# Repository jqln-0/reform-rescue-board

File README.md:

This is a breakout board for an MNT Reform's SOM! It's designed to make it
easier to rescue a bad bootloader flash, or work on the initial bring-up of new
SOMs.

Most of what it breaks out is already available on the Reform motherboard,
however USB1 is exposed as a micro usb port so that it's easy to use
manufacturer tools like `uuu` that rely on USB OTG functionality.

Here is what the PCB looks like in KiCad:

Here is what the PCB looks like in real life:

Here is what an assembled board that's in-use looks like:

(please excuse my bodges; I initially used one wrong part number + one wrong
footprint.)

Note the last picture includes the little STL in `enclosure/`. It's not very
good, but whatever. It'll do.

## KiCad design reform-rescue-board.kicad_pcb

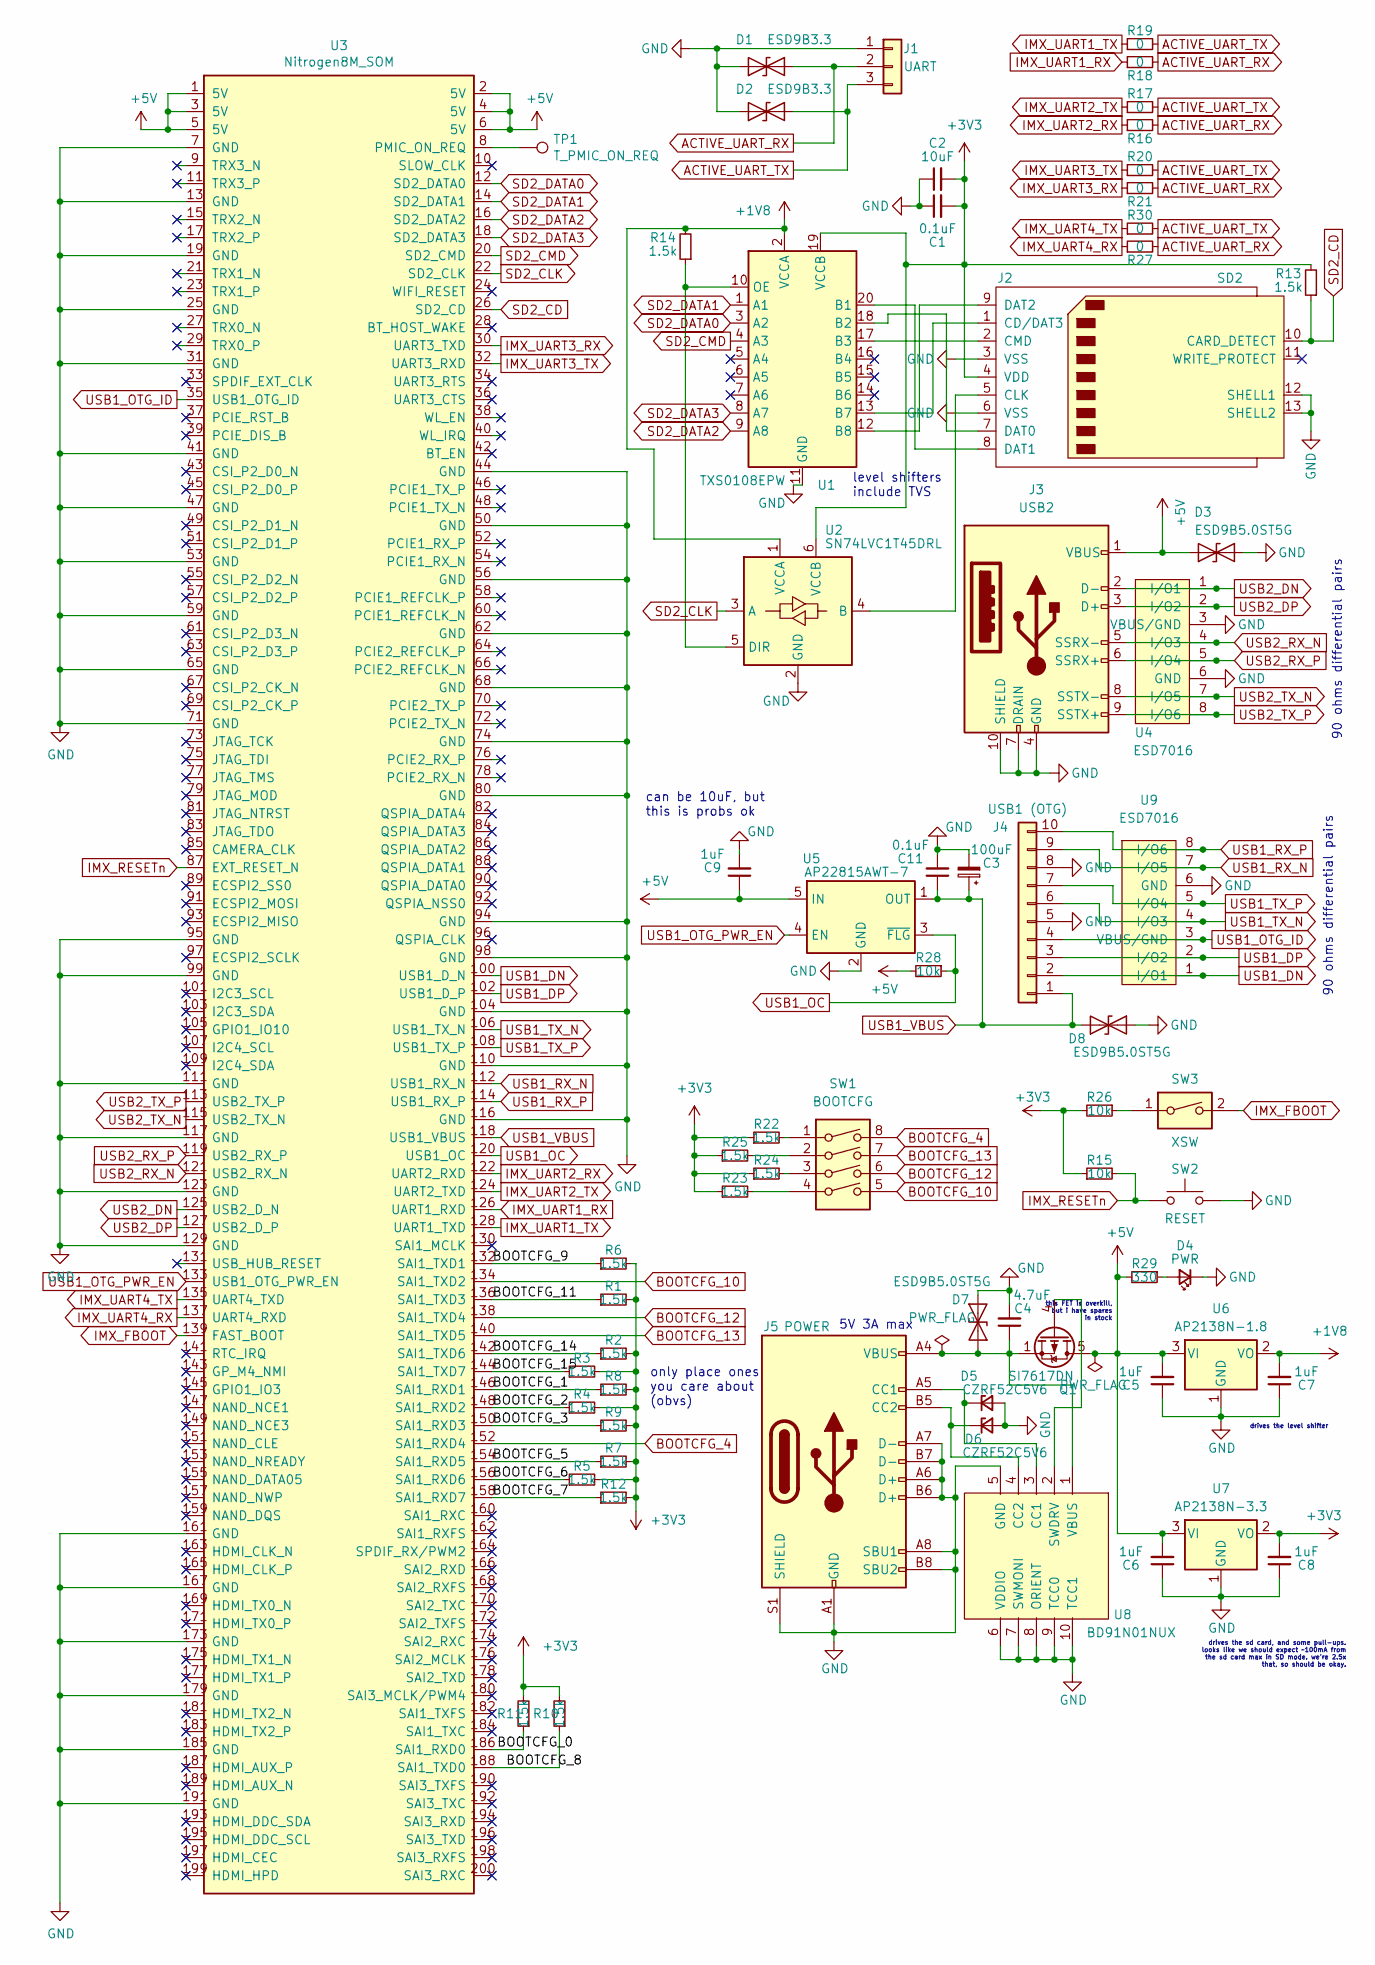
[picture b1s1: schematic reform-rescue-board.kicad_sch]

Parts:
C1, C11: 0.1uF; C_0603_1608Metric_Pad1.08x0.95mm_HandSolder
C2: 10uF; C_0603_1608Metric_Pad1.08x0.95mm_HandSolder
C3: 100uF; CP_Elec_6.3x5.8
C4: 4.7uF; C_0603_1608Metric_Pad1.08x0.95mm_HandSolder
C5, C6, C7, C8, C9: 1uF; C_0603_1608Metric_Pad1.08x0.95mm_HandSolder
D1, D2: ESD9B3.3; D_SOD-923
D3, D7, D8: ESD9B5.0ST5G; D_SOD-923
D4: PWR; D_0603_1608Metric
D5, D6: CZRF52C5V6; D_SOD-323_HandSoldering
J1: UART; PinHeader_1x03_P2.54mm_Vertical
J2: SD2; SD_Kyocera_145638109511859+
J3: USB2; USB3_A_Molex_48393-001
J4: USB1 (OTG); USB3_Micro-B_Connfly_DS1104-01
J5: POWER; USB_C_Receptacle_HRO_TYPE-C-31-M-12
Q1: SI7617DN; Vishay_PowerPAK_1212-8_Single
R1, R2, R3, R4, R5, R6, R7, R8, R9, R10, R11, R12, R13, R14, R22, R23, R24, R25: 1.5k; R_0603_1608Metric_Pad0.98x0.95mm_HandSolder
R15, R26, R28: 10k; R_0603_1608Metric_Pad0.98x0.95mm_HandSolder
R16, R17, R18, R19, R20, R21, R27, R30: 0; R_0603_1608Metric_Pad0.98x0.95mm_HandSolder
R29: 330; R_0603_1608Metric_Pad0.98x0.95mm_HandSolder
SW1: BOOTCFG; SW_DIP_SPSTx04_Slide_Omron_A6S-410x_W8.9mm_P2.54mm
SW2: RESET; SW_SPST_Omron_B3FS-100xP
SW3: XSW; SW_DIP_SPSTx01_Slide_Omron_A6S-110x_W8.9mm_P2.54mm
TP1: T_PMIC_ON_REQ; TestPoint_Pad_D1.0mm
U1: TXS0108EPW; TSSOP-20_4.4x6.5mm_P0.65mm
U2: SN74LVC1T45DRL; SOT-563
U3: Nitrogen8M_SOM; TE_2040910-1
U4, U9: ESD7016; TVS_ESD7016MUTAG
U5: AP22815AWT-7; SOT-23-5
U6: AP2138N-1.8; SOT-23
U7: AP2138N-3.3; SOT-23
U8: BD91N01NUX; VSON-10-1EP_3x3mm_P0.5mm_EP1.65x2.4mm

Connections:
+1V8: C7.2, R14.2, U1.2 (VCCA), U2.1 (VCCA), U6.2 (VO)
+3V3: C1.2, C2.2, C8.2, J2.4 (VDD), R1.2, R2.2, R3.2, R4.2, R5.2, R6.2, R7.2, R8.2, R9.2, R10.2, R11.2, R12.2, R13.2, R15.1, R22.1, R23.1, R24.1, R25.1, R26.2, U1.19 (VCCB), U2.6 (VCCB), U7.2 (VO)
+5V: C5.2, C6.2, C9.1, D3.1 (A1), J3.1 (VBUS), Q1.5 (D), R28.2, R29.2, U3.1 (5V), U3.2 (5V), U3.3 (5V), U3.4 (5V), U3.5 (5V), U3.6 (5V), U5.5 (IN), U6.3 (VI), U7.3 (VI)
/BOOTCFG_0: R11.1, U3.186 (SAI1_RXD0)
/BOOTCFG_1: R8.1, U3.146 (SAI1_RXD1)
/BOOTCFG_2: R4.1, U3.148 (SAI1_RXD2)
/BOOTCFG_3: R9.1, U3.150 (SAI1_RXD3)
/BOOTCFG_5: R7.1, U3.154 (SAI1_RXD5)
/BOOTCFG_6: R5.1, U3.156 (SAI1_RXD6)
/BOOTCFG_7: R12.1, U3.158 (SAI1_RXD7)
/BOOTCFG_8: R10.1, U3.188 (SAI1_TXD0)
/BOOTCFG_9: R6.1, U3.132 (SAI1_TXD1)
/BOOTCFG_11: R1.1, U3.136 (SAI1_TXD3)
/BOOTCFG_14: R2.1, U3.142 (SAI1_TXD6)
/BOOTCFG_15: R3.1, U3.144 (SAI1_TXD7)
ACTIVE_UART_RX: D1.1 (A1), J1.2, R16.2, R18.2, R21.2, R27.2
ACTIVE_UART_TX: D2.1 (A1), J1.3, R17.2, R19.2, R20.2, R30.2
BOOTCFG_4: SW1.8, U3.152 (SAI1_RXD4)
BOOTCFG_10: SW1.5, U3.134 (SAI1_TXD2)
BOOTCFG_12: SW1.6, U3.138 (SAI1_TXD4)
BOOTCFG_13: SW1.7, U3.140 (SAI1_TXD5)
IMX_FBOOT: SW3.2, U3.139 (FAST_BOOT)
IMX_RESETn: R15.2, SW2.1, U3.87 (EXT_RESET_N)
IMX_UART1_RX: R18.1, U3.126 (UART1_RXD)
IMX_UART1_TX: R19.1, U3.128 (UART1_TXD)
IMX_UART2_RX: R16.1, U3.122 (UART2_RXD)
IMX_UART2_TX: R17.1, U3.124 (UART2_TXD)
IMX_UART3_RX: R21.1, U3.30 (UART3_TXD)
IMX_UART3_TX: R20.1, U3.32 (UART3_RXD)
IMX_UART4_RX: R27.1, U3.137 (UART4_RXD)
IMX_UART4_TX: R30.1, U3.135 (UART4_TXD)
unnamed: C4.1, D7.1 (A1), J5.A4 (VBUS), J5.A9 (VBUS), J5.B4 (VBUS), J5.B9 (VBUS), Q1.1 (S), Q1.2 (S), Q1.3 (S), U8.1 (VBUS)
unnamed: D4.2 (A), R29.1
unnamed: D5.1 (K), J5.A5 (CC1), U8.3 (CC1)
unnamed: D6.1 (K), J5.B5 (CC2), U8.4 (CC2)
unnamed: J2.1 (CD/DAT3), U1.13 (B7)
unnamed: J2.2 (CMD), U1.17 (B3)
unnamed: J2.7 (DAT0), U1.18 (B2)
unnamed: J2.8 (DAT1), U1.20 (B1)
unnamed: J2.9 (DAT2), U1.12 (B8)
unnamed: Q1.4 (G), U8.2 (SWDRV)
unnamed: R14.1, U1.10 (OE), U2.5 (DIR)
unnamed: R22.2, SW1.1
unnamed: R23.2, SW1.4
unnamed: R24.2, SW1.3
unnamed: R25.2, SW1.2
unnamed: R26.1, SW3.1
unnamed: TP1.1, U3.8 (PMIC_ON_REQ)
SD2_CD: J2.10 (CARD_DETECT), R13.1, U3.26 (SD2_CD)
SD2_CLK: U2.3 (A), U3.22 (SD2_CLK)
SD2_CMD: U1.4 (A3), U3.20 (SD2_CMD)
SD2_DATA0: U1.3 (A2), U3.12 (SD2_DATA0)
SD2_DATA1: U1.1 (A1), U3.14 (SD2_DATA1)
SD2_DATA2: U1.9 (A8), U3.16 (SD2_DATA2)
SD2_DATA3: U1.8 (A7), U3.18 (SD2_DATA3)
USB1_DN: J4.2, U3.100 (USB1_D_N), U9.1 (I/O1)
USB1_DP: J4.3, U3.102 (USB1_D_P), U9.2 (I/O2)
USB1_OC: R28.1, U3.120 (USB1_OC), U5.3 (~FLG)
USB1_OTG_ID: J4.4, U3.35 (USB1_OTG_ID), U9.3 (VBUS/GND)
USB1_OTG_PWR_EN: U3.133 (USB1_OTG_PWR_EN), U5.4 (EN)
USB1_RX_N: J4.9, U3.112 (USB1_RX_N), U9.7 (I/O5)
USB1_RX_P: J4.10, U3.114 (USB1_RX_P), U9.8 (I/O6)
USB1_TX_N: J4.6, U3.106 (USB1_TX_N), U9.4 (I/O3)
USB1_TX_P: J4.7, U3.108 (USB1_TX_P), U9.5 (I/O4)
USB1_VBUS: C3.1, C11.1, D8.2 (A2), J4.1, U3.118 (USB1_VBUS), U5.1 (OUT)
USB2_DN: J3.2 (D-), U3.125 (USB2_D_N), U4.1 (I/O1)
USB2_DP: J3.3 (D+), U3.127 (USB2_D_P), U4.2 (I/O2)
USB2_RX_N: J3.5 (SSRX-), U3.121 (USB2_RX_N), U4.4 (I/O3)
USB2_RX_P: J3.6 (SSRX+), U3.119 (USB2_RX_P), U4.5 (I/O4)
USB2_TX_N: J3.8 (SSTX-), U3.115 (USB2_TX_N), U4.7 (I/O5)
USB2_TX_P: J3.9 (SSTX+), U3.113 (USB2_TX_P), U4.8 (I/O6)

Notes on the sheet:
only place ones you care about (obvs)
level shifters include TVS
drives the sd card, and some pull-ups. looks like we should expect ~100mA from the sd card max in SD mode. we're 2.5x that, so should be okay.
90 ohms differential pairs
5V 3A max
this FET is overkill, but i have spares in stock
drives the level shifter
can be 10uF, but this is probs ok

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
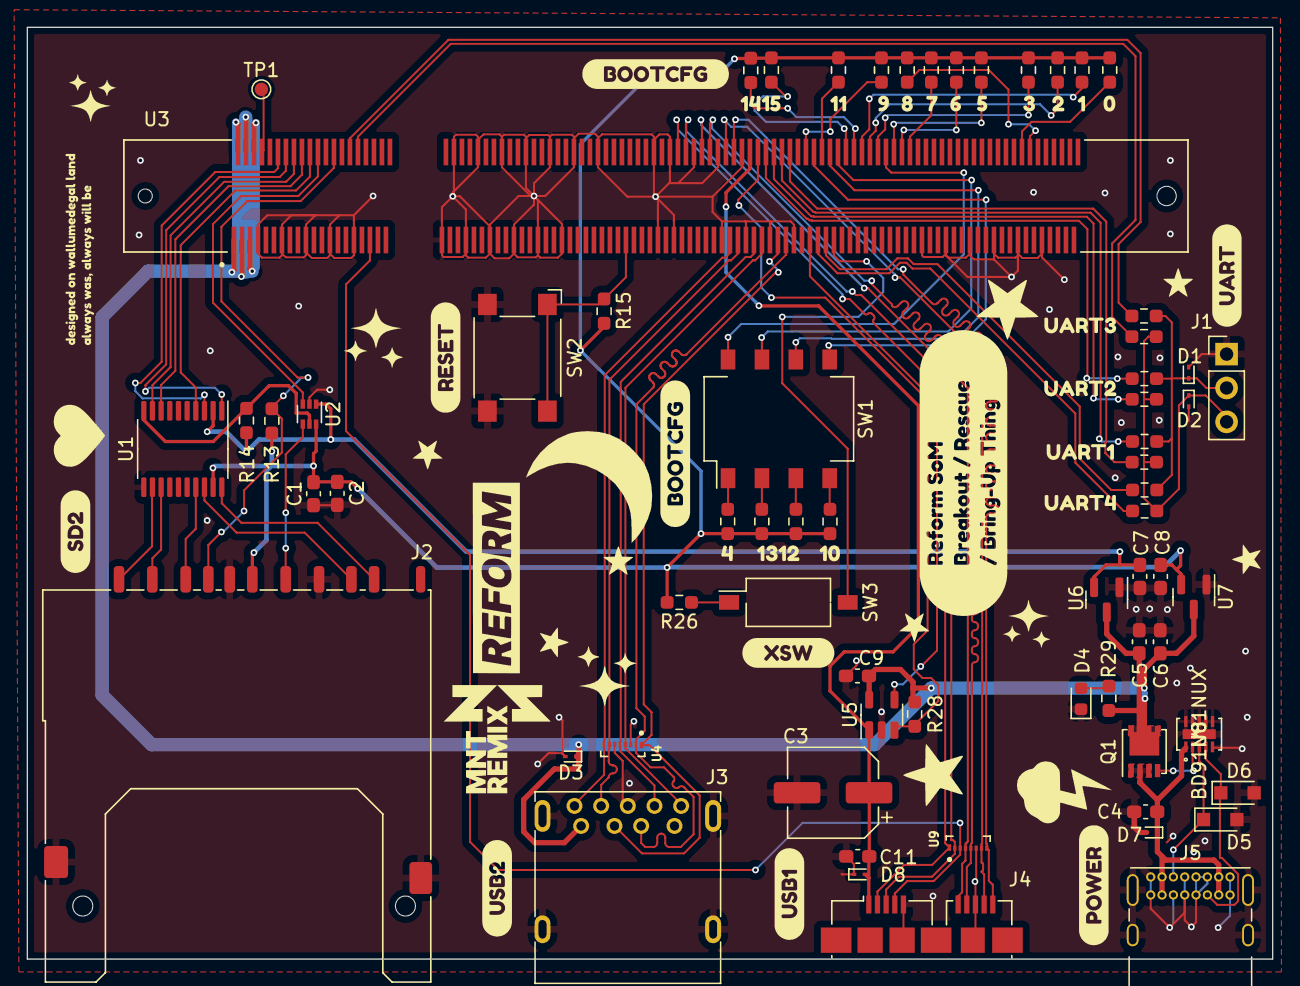
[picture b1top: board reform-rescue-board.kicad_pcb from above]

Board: 2 copper layers, 93.4 x 69.9 mm, 103 parts (0 on the bottom side), 73 nets.

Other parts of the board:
G: LOGO; star_small
G#2, G#3, G#4, G#5, G#6: LOGO; star_small
kibuzzard-62A7FD84, kibuzzard-62A7FD84#2: G***; kibuzzard-62A7FD84
kibuzzard-62A7FDA4: G***; kibuzzard-62A7FDA4
kibuzzard-62A7FDB1: G***; kibuzzard-62A7FDB1
kibuzzard-62A7FDB8: G***; kibuzzard-62A7FDB8
kibuzzard-62A7FDC1: G***; kibuzzard-62A7FDC1
kibuzzard-62A7FDCC: G***; kibuzzard-62A7FDCC
kibuzzard-62A7FDD2: G***; kibuzzard-62A7FDD2
kibuzzard-62A7FDDB: G***; kibuzzard-62A7FDDB
kibuzzard-62A7FDE3: G***; kibuzzard-62A7FDE3
kibuzzard-62A7FDE9: G***; kibuzzard-62A7FDE9
kibuzzard-62A7FDEF: G***; kibuzzard-62A7FDEF
kibuzzard-62A7FE5E: G***; kibuzzard-62A7FE5E
kibuzzard-62A7FE70: G***; kibuzzard-62A7FE70
kibuzzard-62A7FE79: G***; kibuzzard-62A7FE79
kibuzzard-62A7FE86: G***; kibuzzard-62A7FE86
kibuzzard-62A7FEC5: G***; kibuzzard-62A7FEC5
kibuzzard-62A7FF2B: G***; kibuzzard-62A7FF2B
kibuzzard-62A7FF03: G***; kibuzzard-62A7FF03
kibuzzard-62A7FF4E: G***; kibuzzard-62A7FF4E
kibuzzard-62A7FF9A: G***; kibuzzard-62A7FF9A
kibuzzard-62A7FF26: G***; kibuzzard-62A7FF26
kibuzzard-62A7FF56: G***; kibuzzard-62A7FF56
kibuzzard-62A7FFAE: G***; kibuzzard-62A7FFAE
kibuzzard-62A7FFC0: G***; kibuzzard-62A7FFC0
kibuzzard-62A7FFCB: G***; kibuzzard-62A7FFCB
kibuzzard-62A7FFD3: G***; kibuzzard-62A7FFD3
kibuzzard-62A7FFD7: G***; kibuzzard-62A7FFD7
kibuzzard-62A82825: G***; kibuzzard-62A82825
kibuzzard-62A82953: G***; kibuzzard-62A82953

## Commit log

2022-07-02 Initial commit, probably missing footprints
2022-07-02 add a legit seeming license
2022-07-02 Add my little enclosure thing
2022-07-02 Add a cool readme

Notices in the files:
parts and their libraries:
Copyright 2021 Accelerated Designs. All rights reserved.
